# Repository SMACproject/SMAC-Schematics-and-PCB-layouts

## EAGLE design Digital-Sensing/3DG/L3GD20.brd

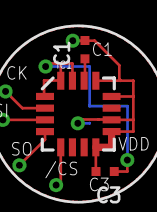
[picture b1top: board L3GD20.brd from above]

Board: 2 copper layers, 5 parts (1 on the bottom side), 3 nets.

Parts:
C1: 1n; C0402
C2: 100n; C0402
C3: 1u; C0402
GOLD_ORB_SM2: OSHWLOGO_REF_SM; OSHW2REF
IC1: L3GD20; LGA16-4X4

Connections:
GND: C1.2, C2.2, C3.2, IC1.8, IC1.9, IC1.10, IC1.12, IC1.13
unnamed: C1.1, IC1.14
VDD: C2.1, C3.1, IC1.1, IC1.15, IC1.16

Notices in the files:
Digital-Sensing/3DG/L3GD20.brd:
CC-BY-SA 3.0
parts and their libraries:
SparkFun-Sensors: Licensing: Creative Commons ShareAlike 4.0 International - https://creativecommons.org/licenses/by-sa/4.0
rc-master-smd: Copyright (C) 2007, Bob Starr
